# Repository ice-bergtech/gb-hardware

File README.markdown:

# Game Boy -related custom hardware by gekkio
Licensed under Creative Commons Attribution 4.0 International.

Used libraries:

* [gekkio-kicad-libs](https://github.com/Gekkio/gekkio-kicad-libs)
* [kicad-footprints](https://github.com/KiCad/kicad-footprints)
* [kicad-symbols](https://github.com/KiCad/kicad-symbols)

## License violations (a.k.a Naughty List)

All the designs in this repository are licensed very liberally under CC BY 4.0,
so you can modify and/or sell them commercially if you want. There's just one
requirement: **attribution**

Basically it just means this: don't remove the original creator's name from the
design. [Here's the full description about it in CC BY 4.0](https://creativecommons.org/licenses/by/4.0/#deed-conditions)

Known license violations:

- Ferrante Crafts: While it wasn't fully intentional and they've
  apologised, they took my GB-CART32K-A design, altered the silkscreen to
  include their name while removing all mention of mine, and then sold these
  carts to people for profit

[Don't be this meme!](https://knowyourmeme.com/memes/i-made-this)

## GB-BENCH-G1

Test bench board for 1st generation Game Boy CPUs (DMG-CPU, SGB-CPU).

* PCB size: 100x100mm
* PCB thickness: any
* Layer count: 4
* Surface finish: any

## GB-BRK-CART

Breakout Game Boy cartridge.

* PCB size: 51.4x61mm
* PCB thickness: 1.0mm
* Layer count: 2
* Surface finish: ENIG (absolutely *do not* choose HASL)

[GB-BRK-CART v4.0 Mouser project for easy part shopping](http://www.mouser.com/ProjectManager/ProjectDetail.aspx?AccessID=61700168c3)

## GB-BRK-CART-PASS

Based on `GB-BRK-CART`.
Allows you to "snoop" on the read and writes the Gameboy is performing on the cartridge.

* PCB size: 51.4x61mm
* PCB thickness: 1.0mm
* Layer count: 2
* Surface finish: ENIG (absolutely *do not* choose HASL)

## GB-BRK-LINK-A

Breakout board for original Game Boy (DMG) link port.

* PCB size: 30x34mm
* PCB thickness: 1.2mm
* Layer count: 2
* Surface finish: any

## GB-BRK-LINK-B

Breakout board for compact link port used in Game Boy Pocket (MGB) and later.

* PCB size: 30x34mm
* PCB thickness: 1.2mm
* Layer count: 2
* Surface finish: any

## GB-BRK-M-XS

Compact male breakout board for the Game Boy cartridge slot.

* PCB size: 51.4x25mm
* PCB thickness: 1.0mm
* Layer count: 2
* Surface finish: ENIG (absolutely *do not* choose HASL)

## GB-BRK-SLOT-A

Breakout board for original Game Boy (DMG) cartridge slot.

* PCB size: 81x80mm
* PCB thickness: 1.2mm
* Layer count: 2
* Surface finish: any

## GB-BRK-SLOT-B

Breakout board for Super Game Boy (SGB) / Super Game Boy 2 (SGB2) cartridge
slot.

* PCB size: 81x80mm
* PCB thickness: 1.2mm
* Layer count: 2
* Surface finish: any

## GB-LIVE32

32 kB ROM-only rapid development cartridge.

* PCB size: 51.4x61mm
* PCB thickness: 1.0mm
* Layer count: 4
* Surface finish: ENIG (absolutely *do not choose HASL*)

[Firmware + software](https://github.com/Gekkio/gb-live32)

[GB-LIVE32 v2.0 Mouser project for easy part shopping](https://www.mouser.com/ProjectManager/ProjectDetail.aspx?AccessID=16281c67ef)

## GB-CART32K-A

Simple ROM-only flash cartridge for 32kx8 PLCC-32 flash (larger chips up to
512kx8 are supported, but only 32k is usable).

* PCB size: 51.4x61mm
* PCB thickness: 1.0mm
* Layer count: 2
* Surface finish: ENIG (absolutely *do not choose HASL*)

## GB-CART256K-A

Simple ROM-only flash cartridge for 128kx8 / 256kx8 PLCC-32 flash.

* PCB size: 51.4x61mm
* PCB thickness: 1.0mm
* Layer count: 2
* Surface finish: ENIG (absolutely *do not choose HASL*)

[Firmware](https://github.com/Gekkio/gb-cart256k-a)

## GB-BRK-CPU-G1

Breakout board for 1st generation Game Boy CPUs (DMG/SGB).

* PCB size: 80x80mm
* PCB thickness: any
* Layer count: 2
* Surface finish: any

## GB-BRK-CPU-G2

Breakout board for 2nd generation Game Boy CPUs (MGB/SGB2).

* PCB size: 80x80mm
* PCB thickness: any
* Layer count: 2
* Surface finish: any

## GB-BRK-TR-A

Breakout board for original Game Boy (DMG) power board transformer.

* PCB size: 24x35mm
* PCB thickness: any
* Layer count: 2
* Surface finish: any

## GB-MBCTEST

Game Boy MBC (Memory Bank Controller) testing cartridge.

* PCB size: 51.4x61mm
* PCB thickness: 1.0mm
* Layer count: 2
* Surface finish: ENIG (absolutely *do not choose HASL*)

## GB-CARTPP-XC

An eXtra Cheap Game Boy cartridge dumper/flasher based on PIC18F45K50.

* PCB size: 80x55mm
* PCB thickness: any (1.0mm recommended)
* Layer count: 2
* Surface finish: any

## GB-CARTPP-DIY

A Game Boy cartridge dumper/flasher based on PIC18F45K50 with DIY-friendly
parts (big and easy to solder).

* PCB size: 100x100mm
* PCB thickness: any
* Layer count: 2
* Surface finish: any

## Notes

### Exporting

For printing the PCBs I've been using JLPCB.

[Gerber Export guide KiCad 5.1](https://jlcpcb.com/help/article/10-How-to-generate-Gerber-and-Drill-files-in-KiCad-5)

When creating a gerber zip, be sure the clear out any old files from previous builds.
This usually happens when files are renamed, and can result in extra files that screw up the printing.

---

They also provide component placement services, just requiring you to export a few extra files.

Generating BOM (Bill of Materials) and CPL (Component Placement List) https://support.jlcpcb.com/article/84-how-to-generate-the-bom-and-centroid-file-from-kicad

Kicad plugins for formatting BOM and CPL: https://github.com/wokwi/kicad-jlcpcb-bom-plugin

Steps:

1.  Open pcb project file in kicad (5.x)
2.  Open schematic
3.  File -> Fabrication Outputs -> BOM
4.  Open PCB viewer
5.  File -> Fabrication Outputs -> Component Placement

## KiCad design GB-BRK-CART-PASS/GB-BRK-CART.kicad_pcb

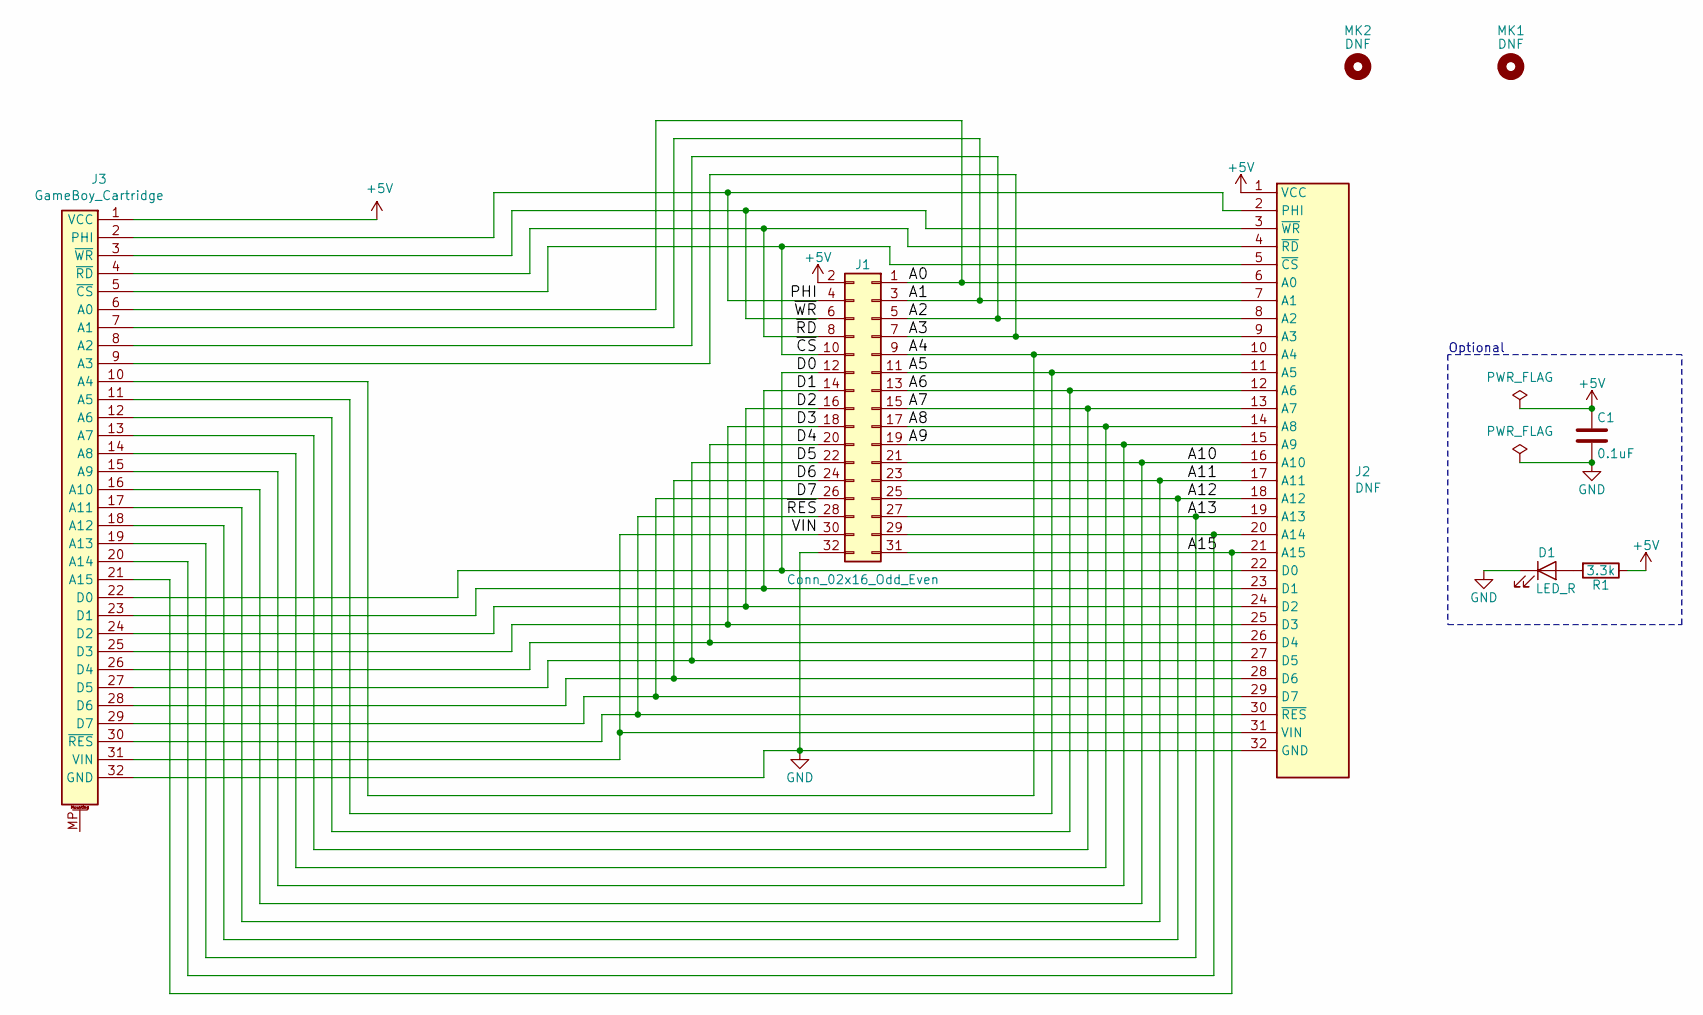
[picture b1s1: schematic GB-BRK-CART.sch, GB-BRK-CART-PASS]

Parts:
C1: 0.1uF; C_0603_1608Metric; Rating 16V X5R; MPN 06035C104KAT4A
D1: LED_R; LED_0603_1608Metric; MPN 150060SS75000
J1: Conn_02x16_Odd_Even; PinHeader_2x16_P2.54mm_Vertical_SMD; MPN 15-91-0800
J2: DNF; GameBoy_Cartridge_1x32_P1.50mm_Edge
J3: GameBoy_Cartridge; GameBoy_Cartridge_AGS_1x32-1MP_P1.50mm_Socket_Horizontal
MK1: DNF; MountingHole_7.2mm
MK2: DNF; MountingHole_2.3mm
R1: 3.3k; R_0603_1608Metric; Rating 1/10W 5%; MPN CRCW06033K30JNEB

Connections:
+5V: C1.1, J1.2, J2.1 (VCC), J3.1 (VCC), R1.1
/A0: J1.1, J2.6 (A0), J3.6 (A0)
/A1: J1.3, J2.7 (A1), J3.7 (A1)
/A2: J1.5, J2.8 (A2), J3.8 (A2)
/A3: J1.7, J2.9 (A3), J3.9 (A3)
/A4: J1.9, J2.10 (A4), J3.10 (A4)
/A5: J1.11, J2.11 (A5), J3.11 (A5)
/A6: J1.13, J2.12 (A6), J3.12 (A6)
/A7: J1.15, J2.13 (A7), J3.13 (A7)
/A8: J1.17, J2.14 (A8), J3.14 (A8)
/A9: J1.19, J2.15 (A9), J3.15 (A9)
/A10: J1.21, J2.16 (A10), J3.16 (A10)
/A11: J1.23, J2.17 (A11), J3.17 (A11)
/A12: J1.25, J2.18 (A12), J3.18 (A12)
/A13: J1.27, J2.19 (A13), J3.19 (A13)
/A15: J1.31, J2.21 (A15), J3.21 (A15)
/D0: J1.12, J2.22 (D0), J3.22 (D0)
/D1: J1.14, J2.23 (D1), J3.23 (D1)
/D2: J1.16, J2.24 (D2), J3.24 (D2)
/D3: J1.18, J2.25 (D3), J3.25 (D3)
/D4: J1.20, J2.26 (D4), J3.26 (D4)
/D5: J1.22, J2.27 (D5), J3.27 (D5)
/D6: J1.24, J2.28 (D6), J3.28 (D6)
/D7: J1.26, J2.29 (D7), J3.29 (D7)
/PHI: J1.4, J2.2 (PHI), J3.2 (PHI)
/VIN: J1.30, J2.31 (VIN), J3.31 (VIN)
/~CS: J1.10, J2.5 (~CS), J3.5 (~CS)
/~RD: J1.8, J2.4 (~RD), J3.4 (~RD)
/~RES: J1.28, J2.30 (~RES), J3.30 (~RES)
/~WR: J1.6, J2.3 (~WR), J3.3 (~WR)
GND: C1.2, D1.1 (K), J1.32, J2.32 (GND), J3.32 (GND), J3.MP
unnamed: D1.2 (A), R1.2
unnamed: J1.29, J2.20 (A14), J3.20 (A14)

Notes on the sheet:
Optional

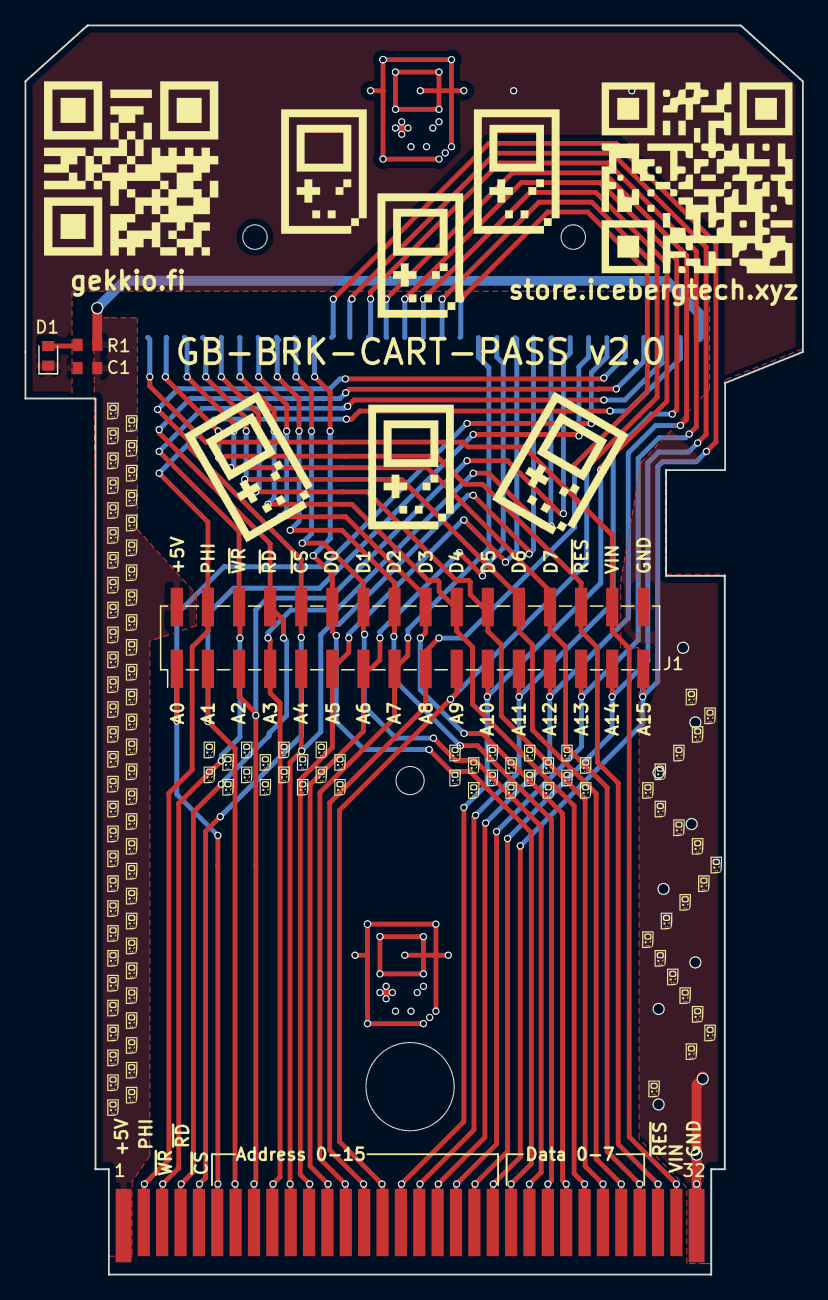
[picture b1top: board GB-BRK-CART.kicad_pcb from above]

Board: 2 copper layers, 63.5 x 102.0 mm, 8 parts (1 on the bottom side), 33 nets.

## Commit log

2023-01-18 Add passthrough cartridge
2023-02-27 Move images around, update breakout/pass cart
2023-02-27 Add case 3d model for printing to breakout pass cart
2023-02-27 Add case top and readme
2023-02-27 Add 3d case model for printing to breakout cart
2023-02-27 Add image of passthrough cart case model
2023-07-27 Add case for gameboy advance type cartridges
